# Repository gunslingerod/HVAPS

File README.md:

View this project on [CADLAB.io](https://cadlab.io/project/2089). 

ATX power supply adaptation for adjustable high voltage output.
Adapter for replacing the TL494 PWM controller.
For use in valve designs tuning.

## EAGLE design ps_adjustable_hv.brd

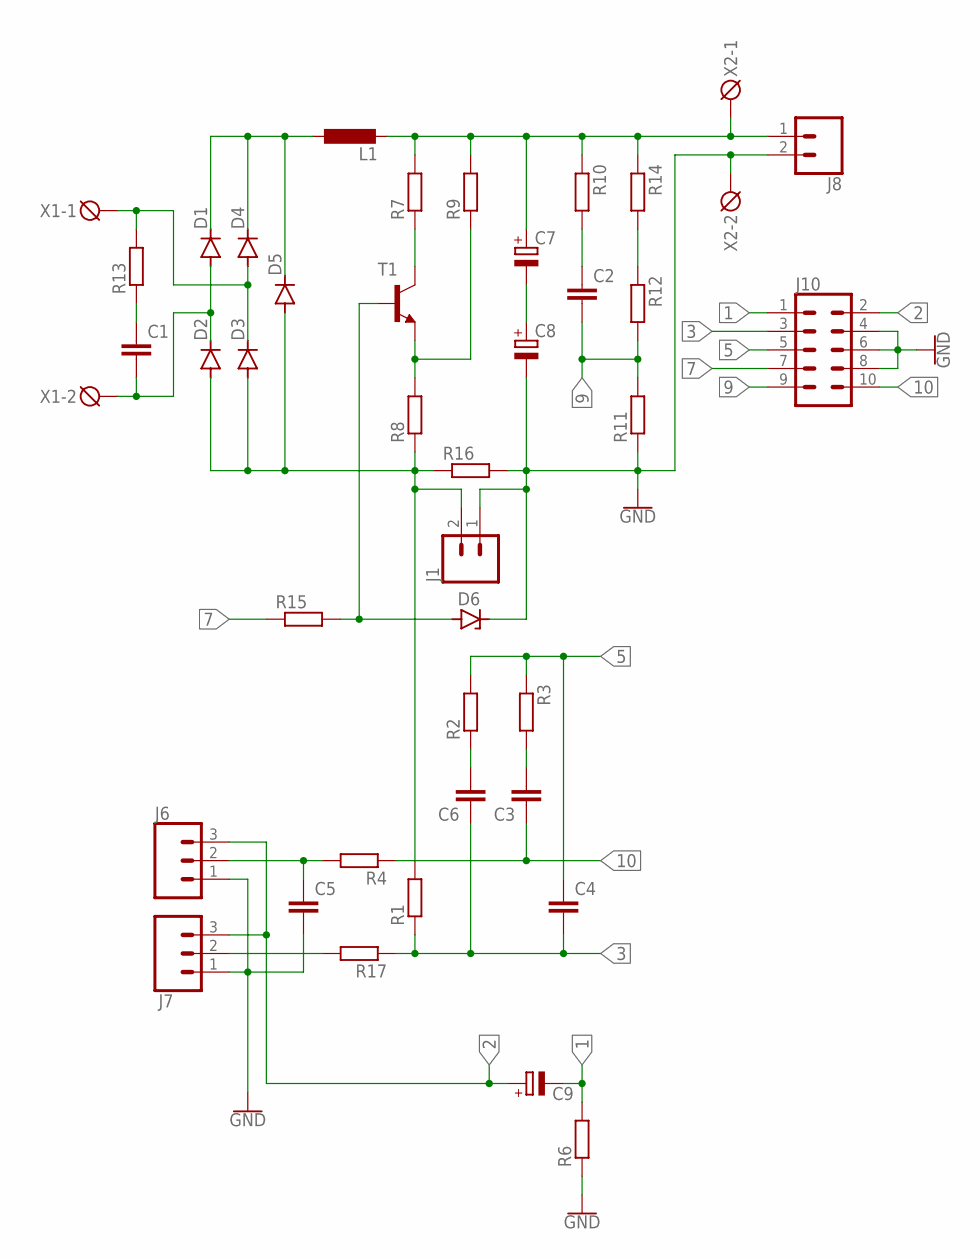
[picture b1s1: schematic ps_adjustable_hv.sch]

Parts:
C1: C-EU050-045X075; C050-045X075
C2: C-EU102-064X133; C102-064X133
C3, C4, C5, C6: C-EUC0805; C0805
C7, C8: CPOL-EUE10-20; EB20D
C9: CPOL-EUE2.5-6; E2,5-6
D1, D2, D3, D4, D5: UF4003; DO41-10
D6: ZENER-DIODEP1-Z12; P1Z12
J1, J8: CONN_02; 1X02
J6, J7: 455-1750-1-ND; 1X03
J10: CONN_05X2SHD; 2X5-SHROUDED
L1: L-EUTJ5-U1; TJ5-U1
R1, R2, R6: R-EU_R0805; R0805
R3, R4, R7, R8, R9, R10, R11, R12, R15, R17: R-EU_VMTA55; VMTA55
R13: R-EU_VMTB60; VMTB60
R14, R16: R-EU_VTA53; VTA53
T1: 2N6517-NPN-TO92-CBE; TO92-CBE
X1, X2: DG3XX-02-5.0; DG306-5.0-02P

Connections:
1: C9.-, J10.1, R6.2
2: C9.+, J6.3, J7.3, J10.2
3: C4.2, C6.1, J10.3, R1.1, R17.1
5: C4.1, J10.5, R2.2, R3.1
7: J10.7, R15.1
9: C2.2, J10.9, R11.2, R12.2
10: C3.1, J10.10, R4.1
GND: C5.2, C8.-, D6.C, J1.1, J6.1, J7.1, J8.2, J10.4, J10.6, J10.8, R6.1, R11.1, R16.2, X2.2
unnamed: C1.1, R13.1
unnamed: C1.2, D1.A, D2.C, X1.2
unnamed: D3.C, D4.A, R13.2, X1.1
unnamed: D2.A, D3.A, D5.A, J1.2, R1.2, R8.1, R16.1
unnamed: R7.1, T1.C
unnamed: R8.2, R9.1, T1.E
unnamed: C7.+, J8.1, L1.2, R7.2, R9.2, R10.1, R14.1, X2.1
unnamed: D1.C, D4.C, D5.C, L1.1
unnamed: C2.1, R10.2
unnamed: R12.1, R14.2
unnamed: C7.-, C8.+
unnamed: D6.A, R15.2, T1.B
unnamed: C3.2, R3.2
unnamed: C6.2, R2.1
unnamed: C5.1, J6.2, R4.2
unnamed: J7.2, R17.2

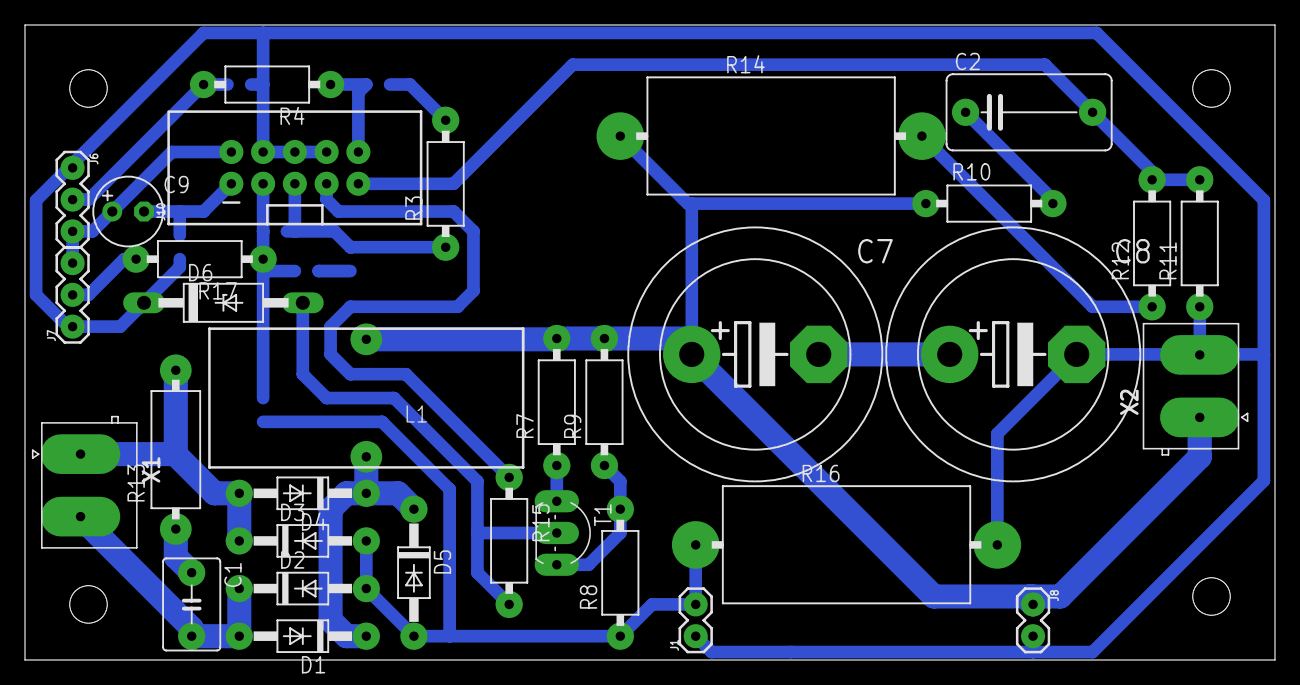
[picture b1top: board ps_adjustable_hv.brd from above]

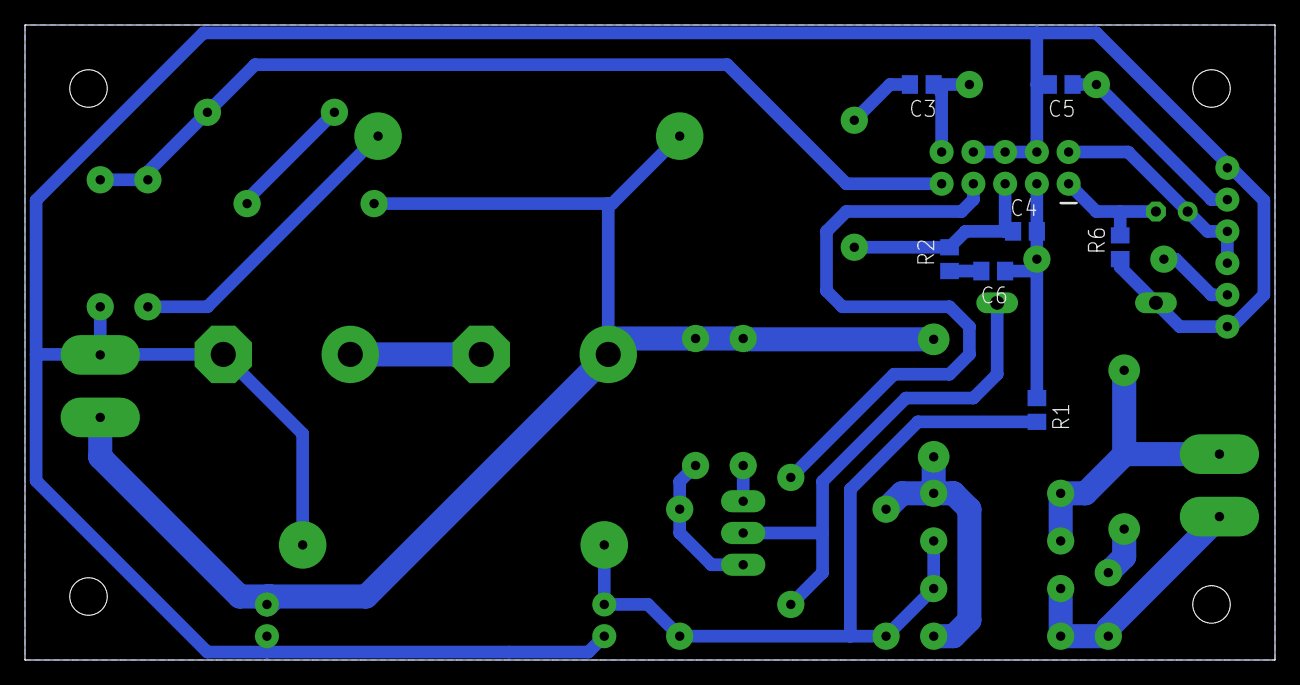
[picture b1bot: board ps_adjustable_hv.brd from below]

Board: 2 copper layers, 100.0 x 50.8 mm, 40 parts (7 on the bottom side), 24 nets.

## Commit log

2019-08-05 Start work on new version of adapter
2019-09-02 Backlink to CADLAB.io has been added.

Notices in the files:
parts and their libraries:
SparkFun-Connectors: Licensing: Creative Commons ShareAlike 4.0 International - https://creativecommons.org/licenses/by-sa/4.0
